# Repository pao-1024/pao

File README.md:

# PAO

> # PAO = PAO Aims Ordnance
>
> 这是一个**递归缩写**（recursive acronym）：全称的第一个词，就是缩写本身。和 `GNU's Not Unix`、`YAML Ain't Markup Language`、`WINE Is Not an Emulator` 一样，它的定义永远指回自己。说不清，也都说得清。

<div align="center">

一台支持语音和网页遥控的小车

<sub>2026 1024 Hackathon · 智能硬件赛道</sub>

<p>

</p>

<p>

</p>

</div>

---

## 它是什么

PAO 使用 ESP32-S3，通过语音或网页控制行驶、测距和电磁发射。

## 实车演示

观看[实车演示视频](docs/making-of.md#演示视频)，包含语音控制、遥控控制和发射测试。装配照片和过程说明见[PAO 制作过程](docs/making-of.md)。

[在线浏览决赛演示稿](https://pao-1024.github.io/pao/)。

## 快速开始

### 在线体验

打开 [PAO 在线模拟器](https://vps-jp.zhangzqs.cn/)，无需本地安装即可预览 3D 小车、OLED 与固件运行状态。点击顶栏“遥控”可用方向按钮或 WASD 驾驶；体验语音时，先点击“启用麦克风和扬声器”并授权，再点击 **BOOT** 开始对话。当前在线版本关闭了语音唤醒，使用 BOOT 按键切换对话。

> 在线服务运行在配置较低的 x86 服务器上，esp32sim 当前尚无 x86 原生 JIT 加速，语音等计算密集操作可能明显卡顿或长时间无响应。**想要更流畅的体验，请参考 [Docker 部署说明](docker/README.md)，在单核性能更好的本机运行模拟器。** 实车交互效果可参考[实车演示视频](docs/making-of.md#演示视频)。

在线演示共享同一台虚拟设备，同一时间仅允许一个浏览器会话使用；看到占用提示时请稍后重试。体验结束后，请关闭模拟器和遥控页面以释放设备。

### Docker 启动

安装 Docker 后，运行以下命令启动完整模拟器（当前支持 Linux amd64）：

```sh
docker run -d --name pao-simulator --stop-timeout 30 \
  -p 127.0.0.1:8080:8000 \
  -v pao-simulator-data:/data \
  ghcr.io/pao-1024/pao-simulator:sha-106b35f
```

首次启动会自动下载镜像，无需克隆源码或安装编译工具。打开 <http://127.0.0.1:8080/>，点击“启用麦克风和扬声器”并允许麦克风权限，按提示完成设备激活。

设备激活后，**点击顶栏的 BOOT 按键即可触发语音对话，也可以说“小炮小炮”唤醒。** 顶栏“遥控”可打开固件遥控页。

停止时运行 `docker stop pao-simulator`，再次启动用 `docker start pao-simulator`，设备状态保存在数据卷中。HTTPS、设备独占、镜像更新和源码构建见 [Docker 部署说明](docker/README.md)；本机开发启动见[模拟器说明](simulator/README.md#启动)。

### 让 AI 帮你启动

复制下面的提示词给能操作终端的 AI：

```text
请按 https://github.com/pao-1024/pao/blob/main/docker/README.md 的本地运行说明，用预构建 Docker 镜像启动完整模拟器。
保持服务运行并保留设备状态；已有容器和数据卷时优先复用，不覆盖或重置设备身份。
确认模拟器页面、后端连接和固件日志正常后，给我访问地址与停止方法；需要设备激活或麦克风授权时提示我。
```

## 系统组成

设备有两条并列控制入口：灵矽服务通过 MCP 调用设备工具，局域网遥控页通过 WebSocket 下发 JSON。两条路径最终汇合到 `PaoBoard`，再进入底盘、测距、发射和外设模块。

```mermaid
flowchart TD
    subgraph McpPath["MCP 控制"]
        direction LR
        Voice["用户语音"] --> Linxi["灵矽服务"] --> Mcp["MCP 工具调用"]
    end

    subgraph WebSocketPath["WebSocket 控制"]
        direction LR
        Web["局域网遥控页"] --> WebSocket["WebSocket /ws"]
    end

    Mcp --> Board
    WebSocket --> Board

    subgraph Firmware["ESP32-S3 PAO 固件"]
        Board["PaoBoard 适配层<br/>参数校验 · 运动状态 · NVS · HTTP"]
        Board --> Chassis["Chassis"]
        Chassis --> Motors["Motor × 2"]
        Motors --> Driver["MX1508"]
        Driver --> Wheels["左右电机"]

        Board --> Distance["ForwardDistanceMover"]
        Distance --> Sensor["HcSr04"]
        Sensor --> Ultrasonic["HC-SR04"]

        Board --> Launcher["Launcher"]
        Launcher --> Relay["继电器"]
        Relay --> Gun["电磁发射器按钮"]

        Board --> Peripherals["OLED · I2S 麦克风与功放 · 状态灯"]
    end

    Firmware -.->|"烧录并运行"| Hardware["实机<br/>真实外设与 Wi-Fi"]
    Firmware -.->|"正式镜像启动"| Simulator["模拟器<br/>ROM + Flash + 外设模型 + 浏览器音频"]
```

## 团队与分工

| 成员 | 分工 |
| --- | --- |
| Zhiqiang Zhang（[@zhangzqs](https://github.com/zhangzqs)） | 硬件设计与组装，底盘、测距及发射驱动，板级集成，固件 CI。 |
| jimyag（[@jimyag](https://github.com/jimyag)） | 构建流程，模拟器内核与界面，语音工具与网页遥控，联调验收。 |

## 功能

- **语音控制**：唤醒词“小炮小炮”；可查询前方距离、前进指定厘米数、自动探索及退出、前后移动、原地转向、停车、开炮、查询设备 IP 和结束对话。
- **网页遥控**：联网后打开设备 IP 对应页面，可用方向按钮或 WASD 驾驶；支持自动探索启停、输出上限、左右轮比例、实时测距和开炮。
- **停车控制**：方向指令带有效期，网页失焦、关闭或断网后不续发；支持立即停止，以及按距离运动和自动探索的超时、测距失败停车。
- **状态显示**：SSD1306 OLED 显示设备状态、表情、对话与访问地址；开发板状态灯和扬声器同步反馈。
- **电磁发射**：语音或网页单次触发；继电器按下发射器按钮，同时播放发射音效。
- **硬件即代码**：用 tscircuit 的 TSX 描述供电、ESP32-S3、麦克风、功放、OLED、超声波、电机驱动和发射器接线，并从源码生成原理图。
- **芯片级模拟**：从 ROM 启动正式固件，显示 OLED、引脚状态、I2C、MCPWM、I2S、串口和可跟随的 3D 小车；支持浏览器麦克风和扬声器。

## 硬件即代码 · Hardware as Code

PAO 用 [tscircuit](https://tscircuit.com/) 的 TSX 组件描述供电、主控、音频、屏幕和电机驱动。模块可以复用，接线变更在 PR 中审查，图纸从源码生成。CI 检查 GPIO、电源、输出连接和图纸一致性。

PAO 参考机的模块接线与原理图见 [ESP32-S3 模块接线图与预览说明](hardware/README.md)。

## 固件 · Voice & Motion

固件基于 ESP-IDF 和小智语音工程，在 ESP32-S3 上完成唤醒词、音频、显示与设备控制。灵矽通过 MCP 调用底盘、测距、电磁发射、网络信息和待机工具；局域网遥控页通过 WebSocket 进入同一套板级控制逻辑。运动参数保存在 NVS，底盘定时停车、测距失败停车和发射继电器脉冲都由设备侧校验与执行。

当前语音角色使用灵矽 AI 智控台，音色、完整提示词和应用步骤见[PAO 语音助手配置](docs/agent.md)。

GPIO、板型、语音工具、局域网遥控、构建方式和实机接入说明见[固件说明](firmware/README.md)。

## 模拟器 · Firmware in the Loop

模拟器使用 Rust、esp32sim 和仓库中的 PAO 板型，从芯片 ROM 启动正式固件。OLED 画面来自固件的 I2C 写入，3D 小车位姿由 MCPWM 输出计算，HC-SR04 回波送入正式 RMT 驱动。页面显示接线状态、I2C、PWM、I2S、UART 和底盘指令，电脑麦克风与扬声器用于语音交互。

[观看模拟器使用演示](https://github.com/user-attachments/assets/b82adcdc-420b-4e07-abb6-0e4ae3ad228b)：在浏览器里通过语音控制正式固件，并查看 OLED、3D 小车、I2C、PWM、I2S 和日志。

启动、配网、语音验证、底盘验收和模拟器架构见[模拟器说明](simulator/README.md)，也可通过 [Docker Compose](docker/README.md) 部署完整模拟器与 HTTPS 入口。

## 机械发射器实验

使用 CadQuery 生成同轴三孔料盘、三凸轮环、弹簧或皮筋击针及炮管的 STEP 装配与分件 STL，用 PyBullet 验证一台电机驱动的三球连续供弹和发射。模型、打印件、参数、运行入口与验证边界见[机械发射器说明](mechanical/cadquery-launcher/README.md)。实物电机、弹性件与打印公差仍需试装验证。

## 没有硬件，也能开始设计与验证

PAO Studio 是实验性的模块化硬件开发工作台，PAO 语音小车是它的首个验证产品，用于验证模块组合、接线检查、固件编译、仿真和实物运行的流程。

Agent 可根据自然语言需求选择模块、自动接线，生成原理图、PCB 制造文件和业务固件，再根据检查、编译和仿真报错修改工程。模块使用实际引脚、驱动和仿真模型，支持内置模块组合与软件在环（Software-in-the-Loop，SIL）场景验收。

实物模块到手前，可以检查供电、公共地、复位、负载、引脚和总线地址，并运行编译后的固件。打板前，可以检查模块封装、布局、铜线连接和制造规则。

当前 PCB 输出是指定模块的安装板。仿真覆盖已建模的数字接口与业务行为，温升、射频、声学、机械负载和实际测量精度仍需实物验证。使用方法和支持范围见 [PAO Studio](experimental/platform/README.md)。

## 未来方向与商业化规划

后续工作面向独立开发者和小型硬件团队，计划复用 PAO 已验证的模块、驱动和工程方案，用于采购、组装和打板前的设计检查。

- 产品规划：扩展模块与驱动，提供可复用的设备方案和批量 SIL 回归。
- 验证规划：把软件检查与硬件在环（Hardware-in-the-Loop，HIL）、样板装配和实物测量结合，核对模型与真实设备的差异。
- 商业化探索：评估团队协作、托管编译与仿真、私有模块库及工程交付支持的付费需求。当前仍是本地实验性工作台，上述付费服务尚在规划中。

产品阶段、商业化假设与验证方式见[硬件开发平台规划](docs/platform-roadmap.md)。

---

<div align="center">
<sub>Talk is cheap. We shoot anyway.</sub>
</div>

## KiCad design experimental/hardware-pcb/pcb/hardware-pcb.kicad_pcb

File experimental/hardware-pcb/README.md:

# PAO 实验性一体化 PCB

本目录使用 tscircuit 描述 120 × 90 mm、四层的 PAO 主板。电池充电与保护、5 V 升压、3.3 V 降压、ESP32-S3、SPI Flash、双路电机驱动、I²S 麦克风与功放、OLED 驱动及 USB-C 都在主板上。测距保留 **HC-SR04-33 超声波模组**，通过四针插座连接。四角预留 3.2 mm 安装孔，内层 1 为地平面。

预览图隐藏了内层地铜，以便查看各层走线；[KiCad PCB](pcb/hardware-pcb.kicad_pcb) 保留完整铜层。

设计基于 `hardware/` 中的功能和 `firmware/boards/pao/config.h` 的 GPIO 分配。`hardware/` 里的电磁发射器和继电器未纳入本板；GPIO18 留空，没有发射器接口或驱动电路。

## 接口

| 接口                  | 用途                                                   | 限制                                                     |
| --------------------- | ------------------------------------------------------ | -------------------------------------------------------- |
| J_BAT                 | 1S 锂电池：1 = 正极、2 = 负极、3 = 10 kΩ NTC           | 须核对电池线序；没有 NTC 时充电温度检测不能正常工作      |
| J_MOTOR_R / J_MOTOR_L | 两路 5 V 直流电机                                      | 上电前核对堵转电流与 DRV8833、升压器、电池及连接器额定值 |
| J_SPEAKER             | 差分扬声器输出                                         | 两端均不能接地                                           |
| J_US                  | 3.3 V HC-SR04-33：1 = VCC、2 = TRIG、3 = ECHO、4 = GND | 只可直接接支持 3.3 V 供电及 Echo 电平的版本              |
| J_USB                 | USB-C 5 V 充电及 ESP32-S3 原生 USB                     | 充电时关闭电池负载开关；本板没有充电电源路径管理         |
| J_RF                  | U.FL 外接 2.4 GHz 天线                                 | 射频匹配元件需依据实板和天线调试                         |

J_US 使用 Samtec `SSW-104-01-G-S` 2.54 mm 四针母座，Trig 接 GPIO8、Echo 接 GPIO9，保留现有固件时序。普通 5 V HC-SR04 的 Echo 可能高于 ESP32-S3 允许电压，不能按本接口直接插接。[HC-SR04-33 数据手册](https://cdn.sparkfun.com/assets/a/8/9/c/a/HC-SR04-33_Datasheet.pdf)、[Samtec 插座 PCB 孔位](https://mm.digikey.com/Volume0/opasdata/d220001/medias/docus/6129/ssw-s.pdf)。

## 电路组成

单节电池由 TP4056 充电，BQ29700 和背靠背 MOSFET 提供保护。滑动开关控制高侧 P 沟道 MOSFET，切断升压输入；TPS61088 生成约 5 V，TPS62132 生成 3.3 V。TP4056 的 12 kΩ PROG 电阻对应约 100 mA 充电电流；装配前须按选定电池重新核算。电机使用 DRV8833 替代原 MX1508 模组，但保留 GPIO11–14 的两路控制分配。麦克风使用 INMP441，功放使用 MAX98357A；状态灯由 GPIO48 驱动 WS2812B-2020。OLED 使用 `UG-2864HSWEG01` 的 30 极裸屏并在板上配置 SSD1306 所需外围，0.7 mm FPC 焊接接点需要与屏厂确定热压工艺及机械固定方式。

除超声波传感器及外接电池、电机、扬声器、天线外，电路功能由板上元件实现。若电机、扬声器、电池型号变化，应重新核对电流、热设计和连接器线序。[ESP32-S3 设计指南](https://documentation.espressif.com/esp-hardware-design-guidelines/en/latest/esp32s3/index.html)、[TPS61088 数据手册](https://www.ti.com/lit/ds/symlink/tps61088.pdf)、[CSD25402Q3A 数据手册](https://www.ti.com/lit/ds/symlink/csd25402q3a.pdf)、[OLED 数据手册](https://www.mouser.com/datasheet/2/737/UG_2864HSWEG01-2489760.pdf)。

## 构建与验证

需要 Node.js 24+、pnpm 10.32.1、Bun 和 Go Task。进入 `experimental/hardware-pcb/` 后运行：

```sh
task setup
task check
```

`task check` 检查格式、代码、网络表、摆放、布线、铜层短路和走线风格；`task build` 单独生成工程，`task bom` 更新 `BOM.csv`，`task dev` 启动预览。在仓库根目录调用时加 `hardware-pcb:` 前缀，例如 `task hardware-pcb:check`。

`pcb/` 保存可直接用 KiCad 打开的 PCB 与七页原理图；`task build` 的新产物位于 `dist/hardware-pcb/`，更新已提交的 KiCad 工程时需同步对应文件。原理图、电路源码、KiCad 工程及检查结果用于设计审阅；投入生产前需要完成实物尺寸确认、PCB DRC、USB 差分阻抗与走线长度检查、射频匹配、电源满载与堵转测试，以及 OLED 装配试验。本设计未经过实物验证。USB 静电保护器的 SOT-23-6 三维模型尚未包含在工程中，不影响二维 PCB 和原理图。

原理图自动排版检查仍会提示少量标签碰撞、电容分组及较长的接地标注路径，需要在 KiCad 中人工整理后再用于生产文档。

`BOM.csv` 列出所有板上器件的标称值和已经选定的制造商料号；未标料号的阻容件仍需按电压、容差和温度范围选型。电池与电机型号未确定，电源、电机铜线宽度及过孔载流能力仍需按实际电流和选定板厂层叠复核。

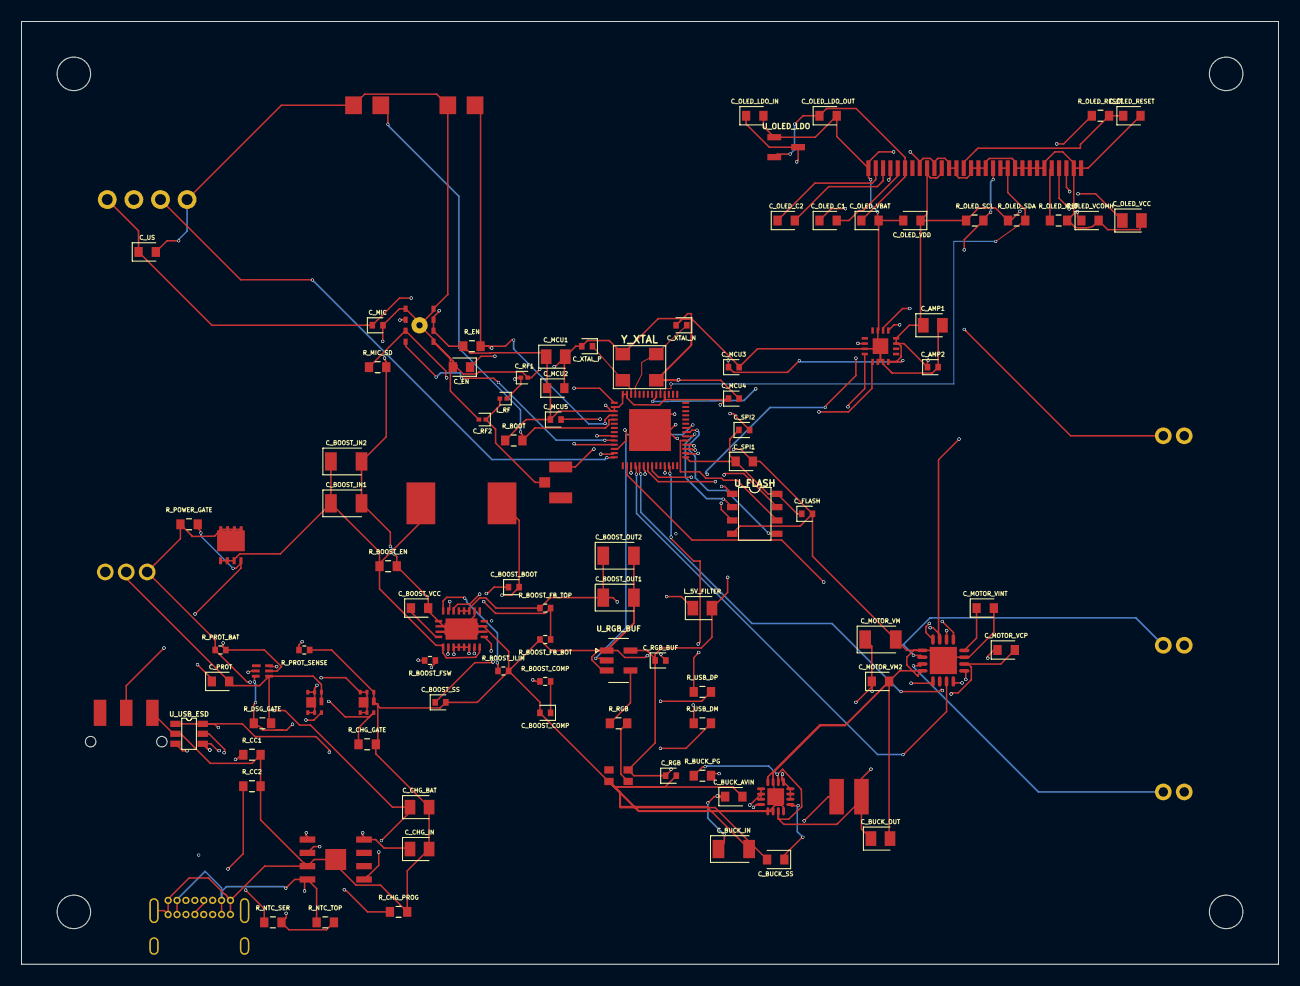
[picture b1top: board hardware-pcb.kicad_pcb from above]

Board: 4 copper layers, 120.0 x 90.0 mm, 106 parts (0 on the bottom side), 82 nets.

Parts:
C_AMP1: 10uF; capacitor_cap0805
C_AMP2: 100nF; capacitor_cap0402
C_BOOST_BOOT: 100nF; capacitor_cap0402
C_BOOST_COMP: 4.7nF; capacitor_cap0402
C_BOOST_IN1, C_BOOST_IN2: 22uF; capacitor_cap1206
C_BOOST_OUT1, C_BOOST_OUT2: 22uF; capacitor_cap1206
C_BOOST_SS: 47nF; capacitor_cap0402
C_BOOST_VCC: 4.7uF; capacitor_cap0603
C_BUCK_AVIN: 100nF; capacitor_cap0603
C_BUCK_IN: 10uF; capacitor_cap1206
C_BUCK_OUT: 22uF; capacitor_cap0805
C_BUCK_SS: 3.3nF; capacitor_cap0603
C_CHG_BAT: 10uF; capacitor_cap0805
C_CHG_IN: 10uF; capacitor_cap0805
C_EN: 1uF; capacitor_cap0603
C_FLASH: 100nF; capacitor_cap0402
C_MCU1: 10uF; capacitor_cap0805
C_MCU2: 1uF; capacitor_cap0603
C_MCU3, C_MCU4, C_MCU5: 100nF; capacitor_cap0402
C_MIC: 100nF; capacitor_cap0402
C_MOTOR_VCP: 10nF; capacitor_cap0603
C_MOTOR_VINT: 2.2uF; capacitor_cap0603
C_MOTOR_VM: 22uF; capacitor_cap1206
C_MOTOR_VM2: 100nF; capacitor_cap0603
C_OLED_C1, C_OLED_C2: 1uF; capacitor_cap0603
C_OLED_LDO_IN: 1uF; capacitor_cap0603
C_OLED_LDO_OUT: 1uF; capacitor_cap0603
C_OLED_RESET: 1uF; capacitor_cap0603
C_OLED_VBAT: 1uF; capacitor_cap0603
C_OLED_VCC: 4.7uF; capacitor_cap0805
C_OLED_VCOMH: 2.2uF; capacitor_cap0603
C_OLED_VDD: 1uF; capacitor_cap0603
C_PROT: 100nF; capacitor_cap0603
C_RF1, C_RF2: 1.5pF; capacitor_cap0201
C_RGB: 100nF; capacitor_cap0402
C_RGB_BUF: 100nF; capacitor_cap0402
C_SPI1: 1uF; capacitor_cap0603
C_SPI2: 100nF; capacitor_cap0402
C_US: 100nF; capacitor_cap0603
C_XTAL_N: 10pF; capacitor_cap0402
C_XTAL_P: 10pF; capacitor_cap0402
D_RGB: WS2812B-2020
J_BAT: J_BAT; B3B-PH-K-S_LF_SN
J_MOTOR_L: J_MOTOR_L; B2B-PH-K-S_LF_SN
J_MOTOR_R: J_MOTOR_R; B2B-PH-K-S_LF_SN
J_RF: J_RF; U_FL-R-SMT-1_10
J_SPEAKER: J_SPEAKER; B2B-PH-K-S_LF_SN
J_US: J_US; SSW-104-01-G-S
J_USB: J_USB; USB4085-GF-A
L_5V_FILTER: 0H; BLM21PG300SN1
L_BOOST: 1.2µH; CDMC8D28NP-1R2MC
L_BUCK: 2.2µH; XFL4020-222MEC
L_RF: 2.4nH; inductor_0201
Q_CHG: CSD16301Q2
Q_DSG: CSD16301Q2
Q_POWER: CSD25402Q3A
R_BOOST_COMP: 17.4kΩ; resistor_res0402
R_BOOST_EN: 100kΩ; resistor_res0603
R_BOOST_FB_BOT: 56.2kΩ; resistor_res0402
R_BOOST_FB_TOP: 174kΩ; resistor_res0402
R_BOOST_FSW: 255kΩ; resistor_res0402
R_BOOST_ILIM: 100kΩ; resistor_res0402
R_BOOT: 10kΩ; resistor_res0603
R_BUCK_PG: 100kΩ; resistor_res0603
R_CC1, R_CC2: 5.1kΩ; resistor_res0603
R_CHG_GATE: 5.1MΩ; resistor_res0603
R_CHG_PROG: 12kΩ; resistor_res0603
R_DSG_GATE: 5.1MΩ; resistor_res0603
R_EN: 10kΩ; resistor_res0603
R_MIC_SD: 100kΩ; resistor_res0603
R_NTC_SER: 0Ω; resistor_res0603
R_NTC_TOP: 7.5kΩ; resistor_res0603
R_OLED_IREF: 390kΩ; resistor_res0603
R_OLED_RESET: 10kΩ; resistor_res0603
R_OLED_SCL: 4.7kΩ; resistor_res0603
R_OLED_SDA: 4.7kΩ; resistor_res0603
R_POWER_GATE: 100kΩ; resistor_res0603
R_PROT_BAT: 330Ω; resistor_res0402
R_PROT_SENSE: 2.2kΩ; resistor_res0402
R_RGB: 330Ω; resistor_res0603
R_USB_DM: 22Ω; resistor_res0603
R_USB_DP: 22Ω; resistor_res0603
SW_BOOT: SW_BOOT; B3U-1000P
SW_POWER: JS102011SAQN
SW_RESET: SW_RESET; B3U-1000P
U_AMP: MAX98357AETE+T; MAX98357AETE_T
U_BOOST: TPS61088RHLR
U_BUCK: TPS62132RGTR
U_CHARGER: TP4056-42-ESOP8
U_FLASH: W25Q128JVSIQ
U_MCU: ESP32-S3R8
U_MIC: INMP441ACEZ-R0
U_MOTOR: DRV8833RTYR
U_OLED: UG-2864HSWEG01
U_OLED_LDO: MCP1702T-4002E/CB; MCP1702T-4002E_CB
U_PROTECT: BQ29700DSER
U_RGB_BUF: SN74AHCT1G125DBVR
U_USB_ESD: USBLC6-2SC6
Y_XTAL: Y_XTAL; ABM8G-40_000MHZ-B4Y-T

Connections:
AMP_BCLK: U_AMP.16, U_MCU.21
AMP_DIN: U_AMP.1, U_MCU.12
AMP_LRC: U_AMP.14, U_MCU.22
BAT_NTC: J_BAT.3, R_NTC_SER.1
BAT_TEMP: R_NTC_SER.2, R_NTC_TOP.2, U_CHARGER.1
BOOST_5V: C_BOOST_OUT1.1, C_BOOST_OUT2.1, L_5V_FILTER.1, R_BOOST_FB_TOP.1, U_BOOST.14, U_BOOST.15, U_BOOST.16
BOOST_BOOT: C_BOOST_BOOT.1, U_BOOST.8
BOOST_COMP: R_BOOST_COMP.1, U_BOOST.18
BOOST_COMP_RC: C_BOOST_COMP.1, R_BOOST_COMP.2
BOOST_FB: R_BOOST_FB_BOT.1, R_BOOST_FB_TOP.2, U_BOOST.17
BOOST_FSW: R_BOOST_FSW.1, U_BOOST.3
BOOST_ILIM: R_BOOST_ILIM.1, U_BOOST.19
BOOST_SS: C_BOOST_SS.1, U_BOOST.10
BOOST_SW: C_BOOST_BOOT.2, L_BOOST.2, R_BOOST_FSW.2, U_BOOST.4, U_BOOST.5, U_BOOST.6, U_BOOST.7
BOOST_VCC: C_BOOST_VCC.1, U_BOOST.1
BOOT: R_BOOT.2, SW_BOOT.1, U_MCU.5
BUCK_PG: R_BUCK_PG.2, U_BUCK.4
BUCK_SS: C_BUCK_SS.1, U_BUCK.9
BUCK_SW: L_BUCK.1, U_BUCK.1, U_BUCK.2, U_BUCK.3
CC1: J_USB.3, R_CC1.1
CC2: J_USB.14, R_CC2.1
CELL_N: C_PROT.2, J_BAT.2, Q_DSG.4, Q_DSG.8, R_DSG_GATE.2, U_PROTECT.4
CELL_P: C_CHG_BAT.1, J_BAT.1, Q_POWER.5, Q_POWER.6, Q_POWER.7, Q_POWER.8, Q_POWER.9, R_POWER_GATE.1, R_PROT_BAT.1, U_CHARGER.5
CHG_GATE: Q_CHG.3, R_CHG_GATE.1, U_PROTECT.2
CHG_PROG: R_CHG_PROG.1, U_CHARGER.2
DSG_GATE: Q_DSG.3, R_DSG_GATE.1, U_PROTECT.3
EN: C_EN.1, R_EN.2, SW_RESET.1, U_MCU.4
FLASH_CLK: U_FLASH.6, U_MCU.33
FLASH_CS: U_FLASH.1, U_MCU.32
FLASH_IO0: U_FLASH.5, U_MCU.35
FLASH_IO1: U_FLASH.2, U_MCU.34
FLASH_IO2: U_FLASH.3, U_MCU.31
FLASH_IO3: U_FLASH.7, U_MCU.30
GND: C_AMP1.2, C_AMP2.2, C_BOOST_COMP.2, C_BOOST_IN1.2, C_BOOST_IN2.2, C_BOOST_OUT1.2, C_BOOST_OUT2.2, C_BOOST_SS.2, C_BOOST_VCC.2, C_BUCK_AVIN.2, C_BUCK_IN.2, C_BUCK_OUT.2, C_BUCK_SS.2, C_CHG_BAT.2, C_CHG_IN.2, C_EN.2, C_FLASH.2, C_MCU1.2, C_MCU2.2, C_MCU3.2, C_MCU4.2, C_MCU5.2, C_MIC.2, C_MOTOR_VINT.2, C_MOTOR_VM.2, C_MOTOR_VM2.2, C_OLED_LDO_IN.2, C_OLED_LDO_OUT.2, C_OLED_RESET.2, C_OLED_VBAT.2, C_OLED_VCC.2, C_OLED_VCOMH.2, C_OLED_VDD.2, C_RF1.2, C_RF2.2, C_RGB.2, C_RGB_BUF.2, C_SPI1.2, C_SPI2.2, C_US.2, C_XTAL_N.2, C_XTAL_P.2, D_RGB.2, J_RF.2, J_US.4, J_USB.1, J_USB.8, J_USB.9, J_USB.16, J_USB.17, Q_CHG.4, Q_CHG.8, R_BOOST_EN.2, R_BOOST_FB_BOT.2, R_BOOST_ILIM.2, R_CC1.2, R_CC2.2, R_CHG_GATE.2, R_CHG_PROG.2, R_MIC_SD.2, R_OLED_IREF.2, R_PROT_SENSE.1, SW_BOOT.2, SW_POWER.3, SW_RESET.2, U_AMP.2, U_AMP.3, U_AMP.11, U_AMP.15, U_AMP.17, U_BOOST.13, U_BOOST.20, U_BOOST.21, U_BUCK.5, U_BUCK.6, U_BUCK.8, U_BUCK.15, U_BUCK.16, U_BUCK.17, U_CHARGER.3, U_CHARGER.9, U_FLASH.4, U_MCU.57, U_MIC.4, U_MIC.5, U_MIC.6, U_MIC.9, U_MOTOR.1, U_MOTOR.4, U_MOTOR.11, U_MOTOR.17, U_OLED.1, U_OLED.8, U_OLED.10, U_OLED.12, U_OLED.13, U_OLED.15, U_OLED.16, U_OLED.17, U_OLED.21, U_OLED.22, U_OLED.23, U_OLED.24, U_OLED.25, U_OLED.29, U_OLED.30, U_OLED_LDO.1, U_RGB_BUF.1, U_RGB_BUF.3, U_USB_ESD.2, Y_XTAL.2, Y_XTAL.4
MIC_SCK: U_MCU.10, U_MIC.1
MIC_SD: R_MIC_SD.1, U_MCU.11, U_MIC.2
MIC_WS: U_MCU.9, U_MIC.3
MOTOR_IN1: U_MCU.16, U_MOTOR.14
MOTOR_IN2: U_MCU.17, U_MOTOR.13
MOTOR_IN3: U_MCU.18, U_MOTOR.7
MOTOR_IN4: U_MCU.19, U_MOTOR.8
MOTOR_L_N: J_MOTOR_L.2, U_MOTOR.3
MOTOR_L_P: J_MOTOR_L.1, U_MOTOR.5
MOTOR_R_N: J_MOTOR_R.2, U_MOTOR.2
MOTOR_R_P: J_MOTOR_R.1, U_MOTOR.16
MOTOR_VCP: C_MOTOR_VCP.1, U_MOTOR.9
MOTOR_VINT: C_MOTOR_VINT.1, U_MOTOR.12
OLED_4V: C_OLED_LDO_OUT.1, C_OLED_VBAT.1, U_OLED.6, U_OLED_LDO.2
OLED_C1N: C_OLED_C1.2, U_OLED.5
OLED_C1P: C_OLED_C1.1, U_OLED.4
OLED_C2N: C_OLED_C2.2, U_OLED.3
OLED_C2P: C_OLED_C2.1, U_OLED.2
OLED_IREF: R_OLED_IREF.1, U_OLED.26
OLED_RESET: C_OLED_RESET.1, R_OLED_RESET.2, U_OLED.14
OLED_SCL: R_OLED_SCL.2, U_MCU.48, U_OLED.18
OLED_SDA: R_OLED_SDA.2, U_MCU.47, U_OLED.19, U_OLED.20
OLED_VCC: C_OLED_VCC.1, U_OLED.28
OLED_VCOMH: C_OLED_VCOMH.1, U_OLED.27
POWER_GATE: Q_POWER.4, R_POWER_GATE.2, SW_POWER.2
PROT_BAT: C_PROT.1, R_PROT_BAT.2, U_PROTECT.5
PROT_MID: Q_CHG.1, Q_CHG.2, Q_CHG.5, Q_CHG.6, Q_CHG.7, Q_DSG.1, Q_DSG.2, Q_DSG.5, Q_DSG.6, Q_DSG.7
PROT_SENSE: R_PROT_SENSE.2, U_PROTECT.6
RF_ANT: C_RF2.1, J_RF.1, L_RF.2
RF_IN: C_RF1.1, L_RF.1, U_MCU.1
RGB_DATA: U_MCU.36, U_RGB_BUF.2
RGB_DATA_5V: R_RGB.1, U_RGB_BUF.4
RGB_DIN: D_RGB.3, R_RGB.2
SPK_N: J_SPEAKER.2, U_AMP.10
SPK_P: J_SPEAKER.1, U_AMP.9
SYS_BAT: C_BOOST_IN1.1, C_BOOST_IN2.1, L_BOOST.1, Q_POWER.1, Q_POWER.2, Q_POWER.3, R_BOOST_EN.1, U_BOOST.2, U_BOOST.9
USB_5V: C_CHG_IN.1, J_USB.2, J_USB.7, J_USB.10, J_USB.15, R_NTC_TOP.1, U_CHARGER.4, U_CHARGER.8, U_USB_ESD.5
USB_DM: R_USB_DM.1, U_MCU.25
USB_DM_CONN: J_USB.5, J_USB.12, R_USB_DM.2, U_USB_ESD.3, U_USB_ESD.4
USB_DP: R_USB_DP.1, U_MCU.26
USB_DP_CONN: J_USB.4, J_USB.13, R_USB_DP.2, U_USB_ESD.1, U_USB_ESD.6
US_ECHO: J_US.3, U_MCU.14
US_TRIG: J_US.2, U_MCU.13
V3V3: C_AMP1.1, C_AMP2.1, C_BUCK_OUT.1, C_MCU1.1, C_MCU2.1, C_MCU3.1, C_MCU4.1, C_MCU5.1, C_MIC.1, C_OLED_VDD.1, C_US.1, J_US.1, L_BUCK.2, R_BOOT.1, R_BUCK_PG.1, R_EN.1, R_OLED_RESET.1, R_OLED_SCL.1, R_OLED_SDA.1, U_AMP.4, U_AMP.7, U_AMP.8, U_BUCK.7, U_BUCK.14, U_MCU.2, U_MCU.3, U_MCU.20, U_MCU.46, U_MCU.55, U_MCU.56, U_MIC.7, U_MIC.8, U_MOTOR.15, U_OLED.9, U_OLED.11
V5: C_BUCK_AVIN.1, C_BUCK_IN.1, C_MOTOR_VCP.2, C_MOTOR_VM.1, C_MOTOR_VM2.1, C_OLED_LDO_IN.1, C_RGB.1, C_RGB_BUF.1, D_RGB.4, L_5V_FILTER.2, U_BUCK.10, U_BUCK.11, U_BUCK.12, U_BUCK.13, U_MOTOR.10, U_OLED_LDO.3, U_RGB_BUF.5
VDD_SPI: C_FLASH.1, C_SPI1.1, C_SPI2.1, U_FLASH.8, U_MCU.29
XTAL_N: C_XTAL_N.1, U_MCU.53, Y_XTAL.3
XTAL_P: C_XTAL_P.1, U_MCU.54, Y_XTAL.1
